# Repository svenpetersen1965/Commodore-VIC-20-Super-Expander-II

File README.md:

# Commodore-VIC-20-Super-Expander-II
This is a reverse engineered  Commodore Super Expander cartridge which does not have the original ROM pinouts, but fits 27C512 EPROMs. The 8k memory bank and the other configuration can be  selected with jumpers or solder bridges.

This cartridge provides a 3k RAM expansion (required for Super Expander) and up to two EPROMs and is of general use for games and especially the VIC-20 diagnostic software.

Please also check my <a href="http://tech.guitarsite.de/vic-20_super_expanderii.html">website</a>.

BOM value (full): 21.39€ (12.12.2020)

# Rev. 1

Rev. 1 allows to select a software size of 4k and 8k. This allows to combine the super expander software with a cartridge that resides at $B000. This requires a multi cartridge box (like the VC-1020). It is for 100% compatibility to teh original. Also a new logo was introduced.

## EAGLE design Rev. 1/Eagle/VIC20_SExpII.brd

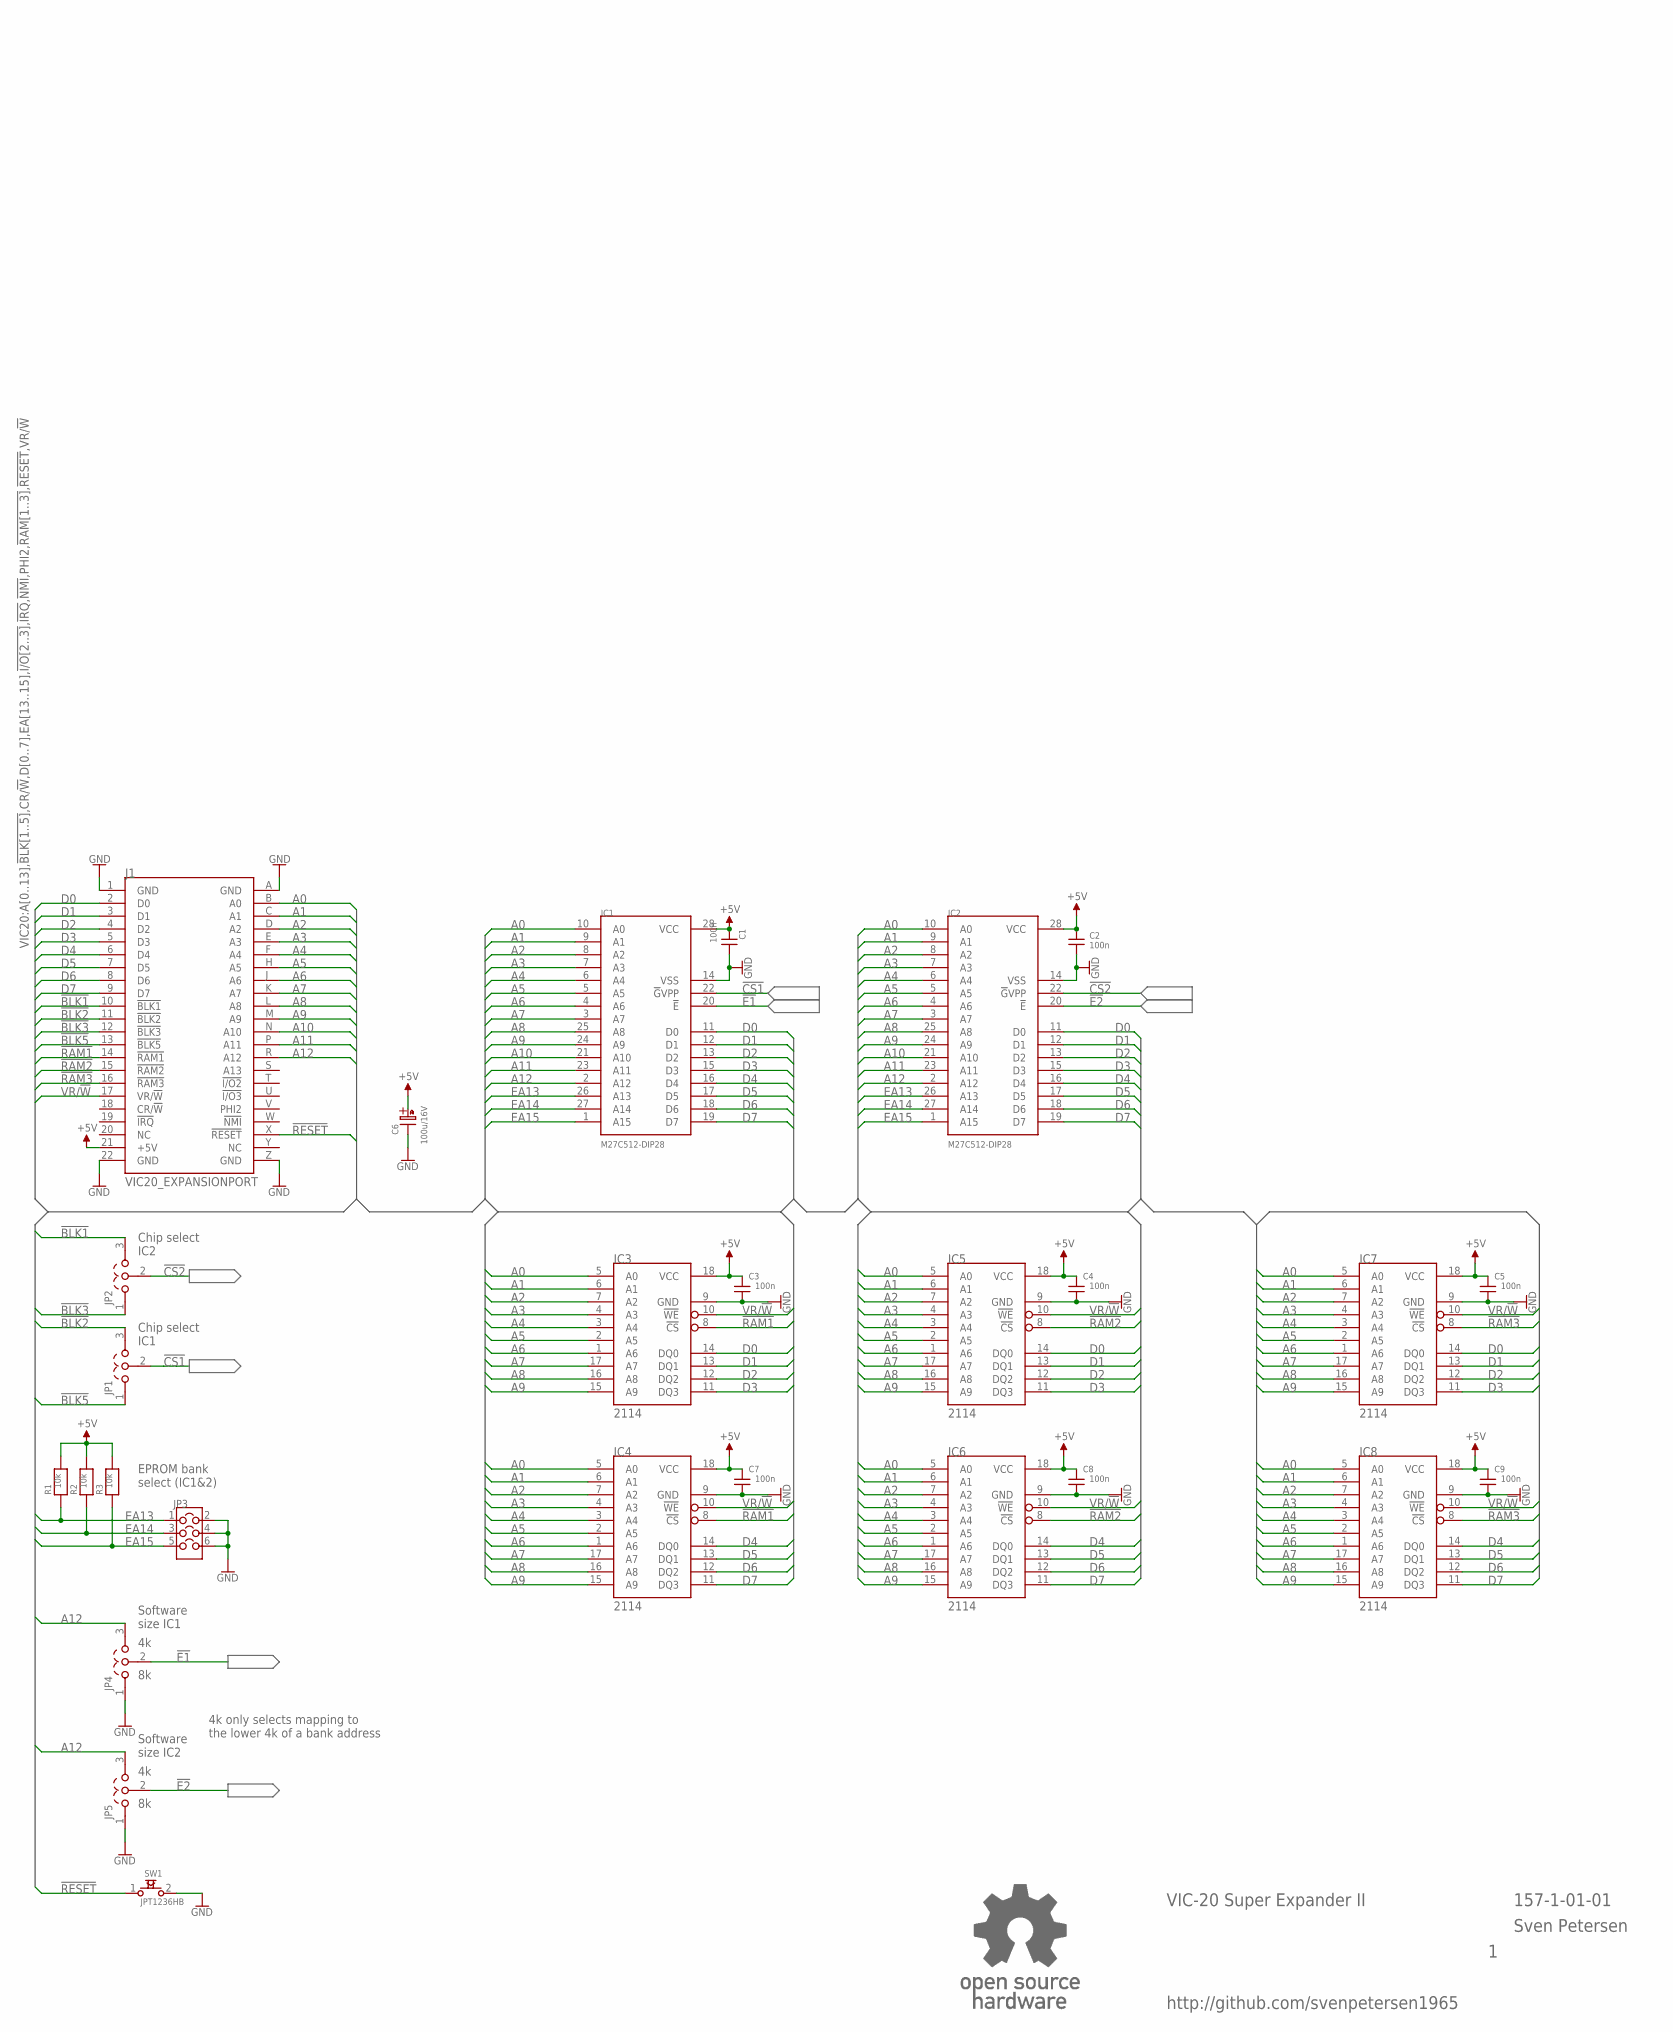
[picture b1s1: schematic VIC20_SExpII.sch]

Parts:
C1, C2, C3, C4, C5, C7, C8, C9: 100n; C-2,5
C6: 100u/16V; C07/2,5
IC1, IC2: M27C512-DIP28; DIL28-6
IC3, IC4, IC5, IC6, IC7, IC8: 2114; DIL18
J1: VIC20_EXPANSIONPORT; VIC20_EXPANSION
JP1, JP2, JP4, JP5: COMBI-3P
JP3: COMBI-3X2P; COMBI-3X2
R1, R2, R3: 10k; R-10
SW1: JPT1236HB; JTP_1236HB
U$2: OPEN_SOURCE_HW; OPENHW

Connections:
!BLK1: J1.10 (!BLK1), JP2.3
!BLK2: J1.11 (!BLK2), JP1.3
!BLK3: J1.12 (!BLK3), JP2.1
!BLK5: J1.13 (!BLK5), JP1.1
!CS1: IC1.22 (!G!VPP), JP1.2
!CS2: IC2.22 (!G!VPP), JP2.2
!E1: IC1.20 (!E), JP4.2
!E2: IC2.20 (!E), JP5.2
!RAM1: IC3.8 (!CS), IC4.8 (!CS), J1.14 (!RAM1)
!RAM2: IC5.8 (!CS), IC6.8 (!CS), J1.15 (!RAM2)
!RAM3: IC7.8 (!CS), IC8.8 (!CS), J1.16 (!RAM3)
!RESET: J1.X (!RESET), SW1.1
+5V: C1.1, C2.1, C3.2, C4.2, C5.2, C6.A (+), C7.2, C8.2, C9.2, IC1.28 (VCC), IC2.28 (VCC), IC3.18 (VCC), IC4.18 (VCC), IC5.18 (VCC), IC6.18 (VCC), IC7.18 (VCC), IC8.18 (VCC), J1.21 (+5V), R1.2, R2.2, R3.2
A0: IC1.10 (A0), IC2.10 (A0), IC3.5 (A0), IC4.5 (A0), IC5.5 (A0), IC6.5 (A0), IC7.5 (A0), IC8.5 (A0), J1.B (A0)
A1: IC1.9 (A1), IC2.9 (A1), IC3.6 (A1), IC4.6 (A1), IC5.6 (A1), IC6.6 (A1), IC7.6 (A1), IC8.6 (A1), J1.C (A1)
A2: IC1.8 (A2), IC2.8 (A2), IC3.7 (A2), IC4.7 (A2), IC5.7 (A2), IC6.7 (A2), IC7.7 (A2), IC8.7 (A2), J1.D (A2)
A3: IC1.7 (A3), IC2.7 (A3), IC3.4 (A3), IC4.4 (A3), IC5.4 (A3), IC6.4 (A3), IC7.4 (A3), IC8.4 (A3), J1.E (A3)
A4: IC1.6 (A4), IC2.6 (A4), IC3.3 (A4), IC4.3 (A4), IC5.3 (A4), IC6.3 (A4), IC7.3 (A4), IC8.3 (A4), J1.F (A4)
A5: IC1.5 (A5), IC2.5 (A5), IC3.2 (A5), IC4.2 (A5), IC5.2 (A5), IC6.2 (A5), IC7.2 (A5), IC8.2 (A5), J1.H (A5)
A6: IC1.4 (A6), IC2.4 (A6), IC3.1 (A6), IC4.1 (A6), IC5.1 (A6), IC6.1 (A6), IC7.1 (A6), IC8.1 (A6), J1.J (A6)
A7: IC1.3 (A7), IC2.3 (A7), IC3.17 (A7), IC4.17 (A7), IC5.17 (A7), IC6.17 (A7), IC7.17 (A7), IC8.17 (A7), J1.K (A7)
A8: IC1.25 (A8), IC2.25 (A8), IC3.16 (A8), IC4.16 (A8), IC5.16 (A8), IC6.16 (A8), IC7.16 (A8), IC8.16 (A8), J1.L (A8)
A9: IC1.24 (A9), IC2.24 (A9), IC3.15 (A9), IC4.15 (A9), IC5.15 (A9), IC6.15 (A9), IC7.15 (A9), IC8.15 (A9), J1.M (A9)
A10: IC1.21 (A10), IC2.21 (A10), J1.N (A10)
A11: IC1.23 (A11), IC2.23 (A11), J1.P (A11)
A12: IC1.2 (A12), IC2.2 (A12), J1.R (A12), JP4.3, JP5.3
D0: IC1.11 (D0), IC2.11 (D0), IC3.14 (DQ0), IC5.14 (DQ0), IC7.14 (DQ0), J1.2 (D0)
D1: IC1.12 (D1), IC2.12 (D1), IC3.13 (DQ1), IC5.13 (DQ1), IC7.13 (DQ1), J1.3 (D1)
D2: IC1.13 (D2), IC2.13 (D2), IC3.12 (DQ2), IC5.12 (DQ2), IC7.12 (DQ2), J1.4 (D2)
D3: IC1.15 (D3), IC2.15 (D3), IC3.11 (DQ3), IC5.11 (DQ3), IC7.11 (DQ3), J1.5 (D3)
D4: IC1.16 (D4), IC2.16 (D4), IC4.14 (DQ0), IC6.14 (DQ0), IC8.14 (DQ0), J1.6 (D4)
D5: IC1.17 (D5), IC2.17 (D5), IC4.13 (DQ1), IC6.13 (DQ1), IC8.13 (DQ1), J1.7 (D5)
D6: IC1.18 (D6), IC2.18 (D6), IC4.12 (DQ2), IC6.12 (DQ2), IC8.12 (DQ2), J1.8 (D6)
D7: IC1.19 (D7), IC2.19 (D7), IC4.11 (DQ3), IC6.11 (DQ3), IC8.11 (DQ3), J1.9 (D7)
EA13: IC1.26 (A13), IC2.26 (A13), JP3.1, R1.1
EA14: IC1.27 (A14), IC2.27 (A14), JP3.3, R2.1
EA15: IC1.1 (A15), IC2.1 (A15), JP3.5, R3.1
GND: C1.2, C2.2, C3.1, C4.1, C5.1, C6.K (-), C7.1, C8.1, C9.1, IC1.14 (VSS), IC2.14 (VSS), IC3.9 (GND), IC4.9 (GND), IC5.9 (GND), IC6.9 (GND), IC7.9 (GND), IC8.9 (GND), J1.1 (GND), J1.22 (GND), J1.A (GND), J1.Z (GND), JP3.2, JP3.4, JP3.6, JP4.1, JP5.1, SW1.2
NC: J1.20 (NC)
VR/!W: IC3.10 (!WE), IC4.10 (!WE), IC5.10 (!WE), IC6.10 (!WE), IC7.10 (!WE), IC8.10 (!WE), J1.17 (VR/!W)

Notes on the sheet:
VIC-20 Super Expander II
157-1-01-01
Sven Petersen
http://github.com/svenpetersen1965
Software size IC1
Software size IC2
EPROM bank select (IC1&2)
Chip select IC1
Chip select IC2
4k only selects mapping to the lower 4k of a bank address

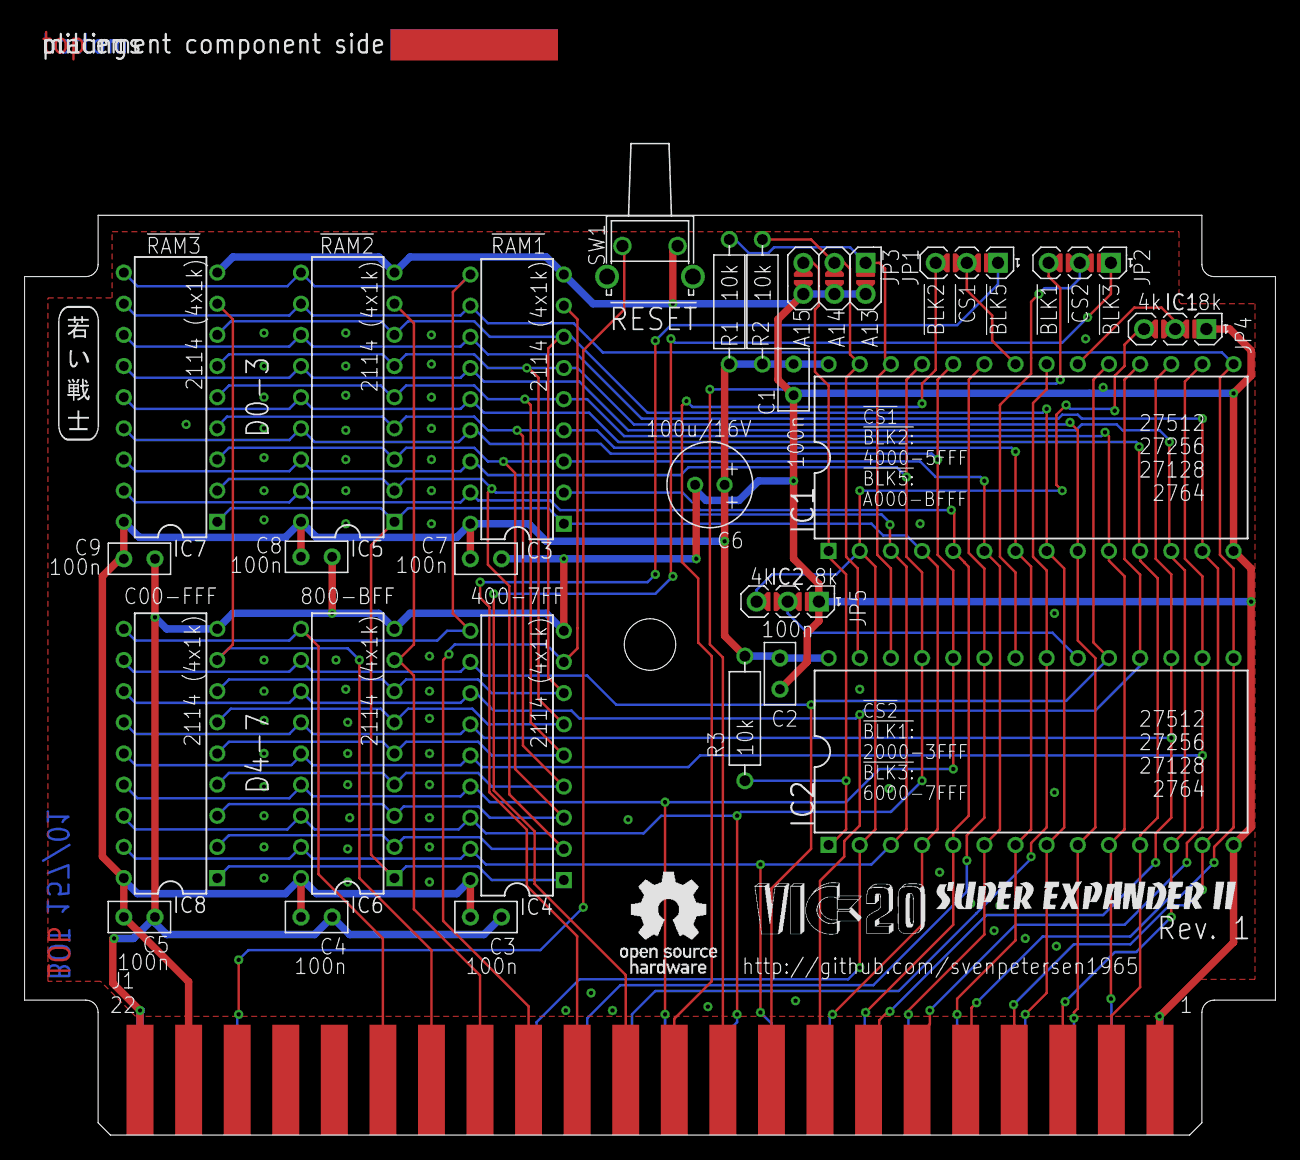
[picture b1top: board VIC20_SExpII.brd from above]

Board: 2 copper layers, 102.0 x 90.6 mm, 33 parts (0 on the bottom side), 39 nets.

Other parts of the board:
U$15: SVEN_TAG
U$16: 2LAYER
U$40: PCB-TITLE/
U$42: SUPER_EXPANDER
U$43: VIC-20

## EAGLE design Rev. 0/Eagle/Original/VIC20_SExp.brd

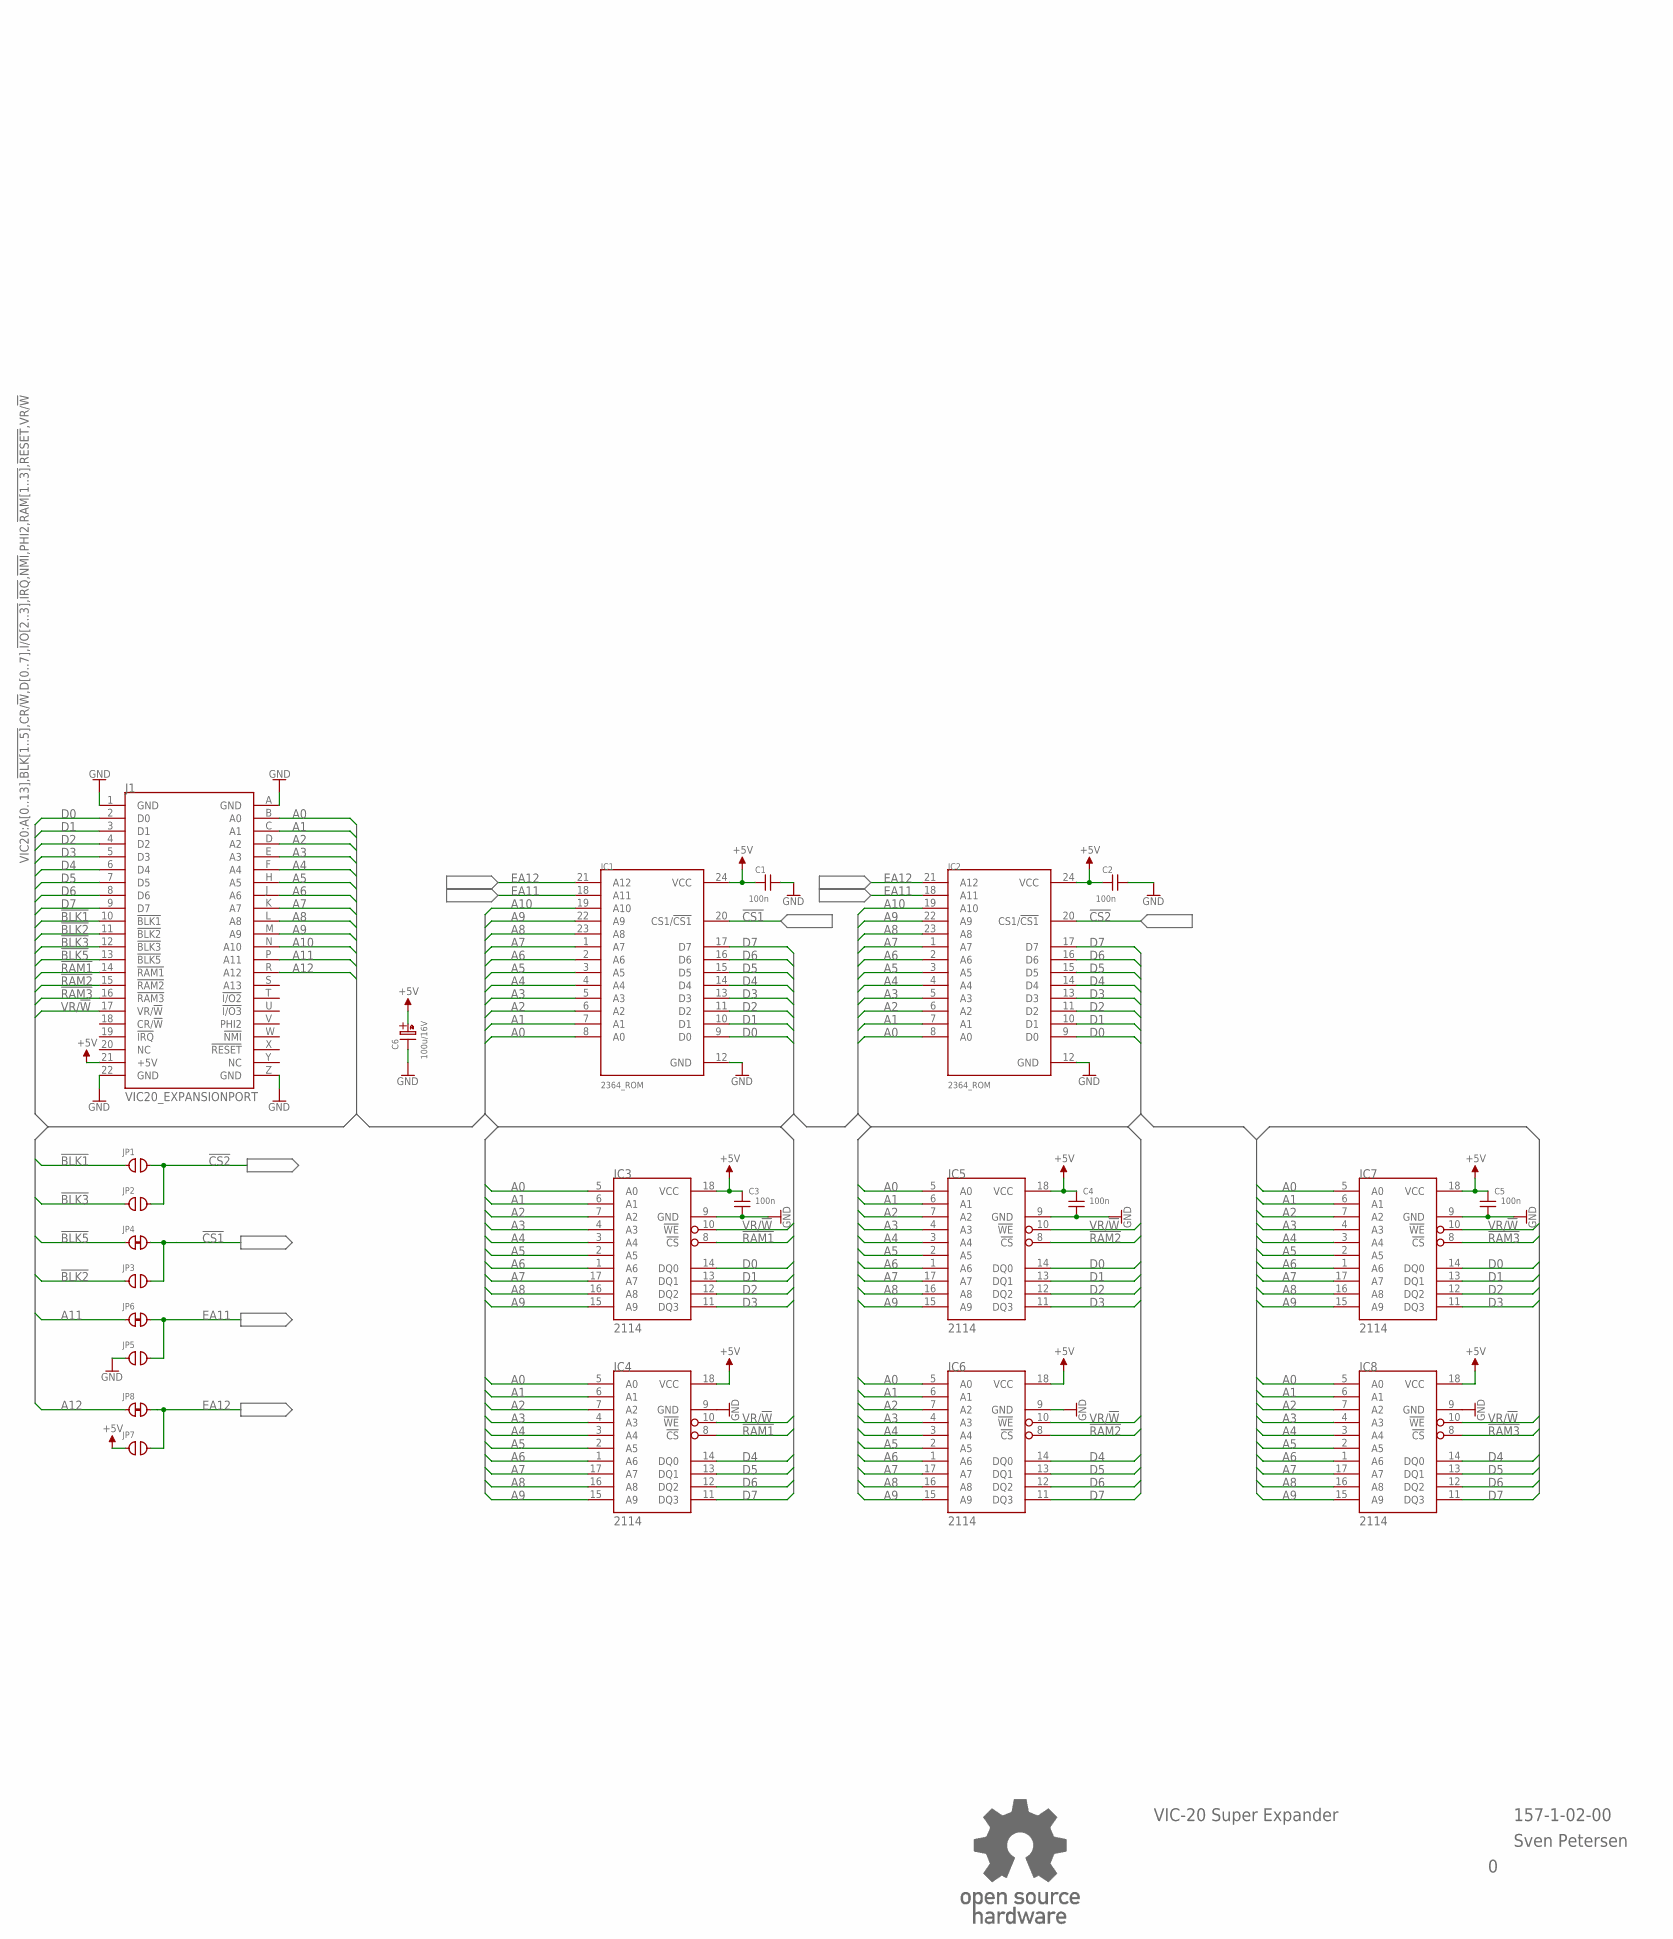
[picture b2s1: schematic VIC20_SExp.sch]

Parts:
C1, C2, C3, C4, C5: 100n; C-2,5
C6: 100u/16V; C07/2,5
IC1, IC2: 2364_ROM; DIL24-6
IC3, IC4, IC5, IC6, IC7, IC8: 2114; DIL18
J1: VIC20_EXPANSIONPORT; VIC20_EXPANSION
JP1, JP2, JP3, JP5, JP7: OPEN; CP_OP
JP4, JP6, JP8: CLOSED; CP_CL
U$2: OPEN_SOURCE_HW; OPENHW

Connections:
!BLK1: J1.10 (!BLK1), JP1.1
!BLK2: J1.11 (!BLK2), JP3.1
!BLK3: J1.12 (!BLK3), JP2.1
!BLK5: J1.13 (!BLK5), JP4.1
!CS1: IC1.20 (CS1/!CS1), JP3.2, JP4.2
!CS2: IC2.20 (CS1/!CS1), JP1.2, JP2.2
!RAM1: IC3.8 (!CS), IC4.8 (!CS), J1.14 (!RAM1)
!RAM2: IC5.8 (!CS), IC6.8 (!CS), J1.15 (!RAM2)
!RAM3: IC7.8 (!CS), IC8.8 (!CS), J1.16 (!RAM3)
+5V: C1.1, C2.1, C3.2, C4.2, C5.2, C6.A (+), IC1.24 (VCC), IC2.24 (VCC), IC3.18 (VCC), IC4.18 (VCC), IC5.18 (VCC), IC6.18 (VCC), IC7.18 (VCC), IC8.18 (VCC), J1.21 (+5V), JP7.1
A0: IC1.8 (A0), IC2.8 (A0), IC3.5 (A0), IC4.5 (A0), IC5.5 (A0), IC6.5 (A0), IC7.5 (A0), IC8.5 (A0), J1.B (A0)
A1: IC1.7 (A1), IC2.7 (A1), IC3.6 (A1), IC4.6 (A1), IC5.6 (A1), IC6.6 (A1), IC7.6 (A1), IC8.6 (A1), J1.C (A1)
A2: IC1.6 (A2), IC2.6 (A2), IC3.7 (A2), IC4.7 (A2), IC5.7 (A2), IC6.7 (A2), IC7.7 (A2), IC8.7 (A2), J1.D (A2)
A3: IC1.5 (A3), IC2.5 (A3), IC3.4 (A3), IC4.4 (A3), IC5.4 (A3), IC6.4 (A3), IC7.4 (A3), IC8.4 (A3), J1.E (A3)
A4: IC1.4 (A4), IC2.4 (A4), IC3.3 (A4), IC4.3 (A4), IC5.3 (A4), IC6.3 (A4), IC7.3 (A4), IC8.3 (A4), J1.F (A4)
A5: IC1.3 (A5), IC2.3 (A5), IC3.2 (A5), IC4.2 (A5), IC5.2 (A5), IC6.2 (A5), IC7.2 (A5), IC8.2 (A5), J1.H (A5)
A6: IC1.2 (A6), IC2.2 (A6), IC3.1 (A6), IC4.1 (A6), IC5.1 (A6), IC6.1 (A6), IC7.1 (A6), IC8.1 (A6), J1.J (A6)
A7: IC1.1 (A7), IC2.1 (A7), IC3.17 (A7), IC4.17 (A7), IC5.17 (A7), IC6.17 (A7), IC7.17 (A7), IC8.17 (A7), J1.K (A7)
A8: IC1.23 (A8), IC2.23 (A8), IC3.16 (A8), IC4.16 (A8), IC5.16 (A8), IC6.16 (A8), IC7.16 (A8), IC8.16 (A8), J1.L (A8)
A9: IC1.22 (A9), IC2.22 (A9), IC3.15 (A9), IC4.15 (A9), IC5.15 (A9), IC6.15 (A9), IC7.15 (A9), IC8.15 (A9), J1.M (A9)
A10: IC1.19 (A10), IC2.19 (A10), J1.N (A10)
A11: J1.P (A11), JP6.1
A12: J1.R (A12), JP8.1
D0: IC1.9 (D0), IC2.9 (D0), IC3.14 (DQ0), IC5.14 (DQ0), IC7.14 (DQ0), J1.2 (D0)
D1: IC1.10 (D1), IC2.10 (D1), IC3.13 (DQ1), IC5.13 (DQ1), IC7.13 (DQ1), J1.3 (D1)
D2: IC1.11 (D2), IC2.11 (D2), IC3.12 (DQ2), IC5.12 (DQ2), IC7.12 (DQ2), J1.4 (D2)
D3: IC1.13 (D3), IC2.13 (D3), IC3.11 (DQ3), IC5.11 (DQ3), IC7.11 (DQ3), J1.5 (D3)
D4: IC1.14 (D4), IC2.14 (D4), IC4.14 (DQ0), IC6.14 (DQ0), IC8.14 (DQ0), J1.6 (D4)
D5: IC1.15 (D5), IC2.15 (D5), IC4.13 (DQ1), IC6.13 (DQ1), IC8.13 (DQ1), J1.7 (D5)
D6: IC1.16 (D6), IC2.16 (D6), IC4.12 (DQ2), IC6.12 (DQ2), IC8.12 (DQ2), J1.8 (D6)
D7: IC1.17 (D7), IC2.17 (D7), IC4.11 (DQ3), IC6.11 (DQ3), IC8.11 (DQ3), J1.9 (D7)
EA11: IC1.18 (A11), IC2.18 (A11), JP5.2, JP6.2
EA12: IC1.21 (A12), IC2.21 (A12), JP7.2, JP8.2
GND: C1.2, C2.2, C3.1, C4.1, C5.1, C6.K (-), IC1.12 (GND), IC2.12 (GND), IC3.9 (GND), IC4.9 (GND), IC5.9 (GND), IC6.9 (GND), IC7.9 (GND), IC8.9 (GND), J1.1 (GND), J1.22 (GND), J1.A (GND), J1.Z (GND), JP5.1
NC: J1.20 (NC)
VR/!W: IC3.10 (!WE), IC4.10 (!WE), IC5.10 (!WE), IC6.10 (!WE), IC7.10 (!WE), IC8.10 (!WE), J1.17 (VR/!W)

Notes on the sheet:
VIC-20 Super Expander
157-1-02-00
Sven Petersen

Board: 2 copper layers, 25 parts (0 on the bottom side), 35 nets, no tracks yet.

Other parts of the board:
U$40: PCB-TITLE/

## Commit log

2020-12-12 Calculation added
2021-06-03 Labels added
2021-07-16 Logo created
2021-07-16 Rev. 1 released
    4k/8k jumper & fancy new logo
2021-08-09 Super Expander Example Software
    typed in from the manual
